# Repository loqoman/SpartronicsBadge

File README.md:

# SpartronicsBadge
The FRC Team 4915 Competition Badge

## Revision One

### Libraries
Some project specific symbols are used (Digikey slide switches). All non kicad-standard libraries used will found under `/lib/` directory, and need to be imported manually from the schematic library manager

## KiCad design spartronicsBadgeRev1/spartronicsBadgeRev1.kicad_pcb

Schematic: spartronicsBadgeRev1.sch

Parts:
BT1, BT2: Battery_Cell; BatteryHolder_Keystone_3034_1x20mm
DE1, DE2, DE3: LED; LED_0603_1608Metric_Pad1.05x0.95mm_HandSolder
DN1, DN2, DN3: LED; LED_0603_1608Metric_Pad1.05x0.95mm_HandSolder
DNE1, DNE2, DNE3: LED; LED_0603_1608Metric_Pad1.05x0.95mm_HandSolder
DNW1, DNW2, DNW3: LED; LED_0603_1608Metric_Pad1.05x0.95mm_HandSolder
DS1, DS2, DS3: LED; LED_0603_1608Metric_Pad1.05x0.95mm_HandSolder
DSE1, DSE2, DSE3: LED; LED_0603_1608Metric_Pad1.05x0.95mm_HandSolder
DSW1, DSW2, DSW3: LED; LED_0603_1608Metric_Pad1.05x0.95mm_HandSolder
DW1, DW2, DW3: LED; LED_0603_1608Metric_Pad1.05x0.95mm_HandSolder
J_Debug1: Conn_02x03; PinHeader_2x03_P2.54mm_Vertical
J_ExtPwr1: Conn_01x02; PinHeader_1x02_P2.54mm_Vertical
RE1, RE2, RE3: 220Ω; R_0603_1608Metric_Pad1.05x0.95mm_HandSolder
RN1, RN2, RN3: 220Ω; R_0603_1608Metric_Pad1.05x0.95mm_HandSolder
RNE1, RNE2, RNE3: 220Ω; R_0603_1608Metric_Pad1.05x0.95mm_HandSolder
RNW1, RNW2, RNW3: 220Ω; R_0603_1608Metric_Pad1.05x0.95mm_HandSolder
RS1, RS2, RS3: 220Ω; R_0603_1608Metric_Pad1.05x0.95mm_HandSolder
RSE1, RSE2, RSE3: 220Ω; R_0603_1608Metric_Pad1.05x0.95mm_HandSolder
RSW1, RSW2, RSW3: 220Ω; R_0603_1608Metric_Pad1.05x0.95mm_HandSolder
RW1, RW2, RW3: 220Ω; R_0603_1608Metric_Pad1.05x0.95mm_HandSolder
S1: JS202011SCQN; Switch_Slide_JS202011SCQN; MPN JS202011SCQN; Digi-Key_PN 401-2002-1-ND
U1: ATmega328PB-AU; TQFP-32_7x7mm_P0.8mm

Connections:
BAT_VCC: BT1.1 (+), J_ExtPwr1.1, S1.3, S1.6
ELED1_SIG: RE1.2, U1.10 (PD6)
ELED2_SIG: RE2.2, U1.3 (PE0)
ELED3_SIG: RE3.2, U1.2 (PD4)
GND: BT2.2 (-), DE1.1 (K), DE2.1 (K), DE3.1 (K), DN1.1 (K), DN2.1 (K), DN3.1 (K), DNE1.1 (K), DNE2.1 (K), DNE3.1 (K), DNW1.1 (K), DNW2.1 (K), DNW3.1 (K), DS1.1 (K), DS2.1 (K), DS3.1 (K), DSE1.1 (K), DSE2.1 (K), DSE3.1 (K), DSW1.1 (K), DSW2.1 (K), DSW3.1 (K), DW1.1 (K), DW2.1 (K), DW3.1 (K), J_Debug1.3, J_ExtPwr1.2, U1.5 (GND), U1.21 (GND)
MISO0: J_Debug1.6, U1.16 (PB4)
MOSI0: J_Debug1.4, U1.15 (PB3)
NC: S1.1, S1.4
NELED1_SIG: RNE1.2, U1.1 (PD3)
NELED2_SIG: RNE2.2, U1.32 (PD2)
NELED3_SIG: RNE3.2, U1.31 (PD1)
NLED1_SIG: RN3.2, U1.28 (PC5)
NLED2_SIG: RN2.2, U1.27 (PC4)
NLED3_SIG: RN1.2, U1.30 (PD0)
NWLED1_SIG: RNW1.1, U1.25 (PC2)
NWLED2_SIG: RNW2.1, U1.26 (PC3)
NWLED3_SIG: RNW3.1, U1.24 (PC1)
unnamed: BT1.2 (-), BT2.1 (+)
unnamed: DE1.2 (A), RE1.1
unnamed: DE2.2 (A), RE2.1
unnamed: DE3.2 (A), RE3.1
unnamed: DN1.2 (A), RN1.1
unnamed: DN2.2 (A), RN2.1
unnamed: DN3.2 (A), RN3.1
unnamed: DNE1.2 (A), RNE1.1
unnamed: DNE2.2 (A), RNE2.1
unnamed: DNE3.2 (A), RNE3.1
unnamed: DNW1.2 (A), RNW1.2
unnamed: DNW2.2 (A), RNW2.2
unnamed: DNW3.2 (A), RNW3.2
unnamed: DS1.2 (A), RS1.2
unnamed: DS2.2 (A), RS2.2
unnamed: DS3.2 (A), RS3.2
unnamed: DSE1.2 (A), RSE1.1
unnamed: DSE2.2 (A), RSE2.1
unnamed: DSE3.2 (A), RSE3.1
unnamed: DSW1.2 (A), RSW1.2
unnamed: DSW2.2 (A), RSW2.2
unnamed: DSW3.2 (A), RSW3.2
unnamed: DW1.2 (A), RW1.2
unnamed: DW2.2 (A), RW2.2
unnamed: DW3.2 (A), RW3.2
RESET: J_Debug1.1, U1.29 (~RESET~/PC6)
SCK0: J_Debug1.5, RSW2.1, U1.17 (PB5)
SELED1_SIG: RSE1.2, U1.14 (PB2)
SELED2_SIG: RSE2.2, U1.8 (XTAL2/PB7)
SELED3_SIG: RSE3.2, U1.6 (PE1)
SLED1_SIG: RS1.1, U1.13 (PB1)
SLED2_SIG: RS2.1, U1.11 (PD7)
SLED3_SIG: RS3.1, U1.12 (PB0)
SWLED1_SIG: RSW1.1, U1.7 (XTAL1/PB6)
SWLED3_SIG: RSW3.1, U1.9 (PD5)
VCC: J_Debug1.2, S1.2, S1.5, U1.4 (VCC)
WLED1_SIG: RW1.1, U1.22 (PE3)
WLED2_SIG: RW2.1, U1.19 (PE2)
WLED3_SIG: RW3.1, U1.23 (PC0)

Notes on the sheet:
North Tooth
North-East Tooth
East Tooth
South-East Tooth
South Tooth
West Tooth
North-West Tooth
LED Specifications:
LED Specifications
SML-LX0603SYW
20mA current
2V drop
Optional External Power
Coin cell symbols need to be assoicated with coin cell clips on netlist
Calculations for Resistors
- Resistors need to drop approx 3v
- Solve Ohms law for R when I = .02, and V = 5
- R = 5 / .02 = 250 Ω
On layout, Resistors should be renamed
Ground Plane
Label On Sickscreen
Later Revisions add reverse protection(shotkeyy) diode here?
South-West Tooth
220 ohm used due to DigiKey stock
Nb: Pin assignments look haphazard, but correspond to footprint

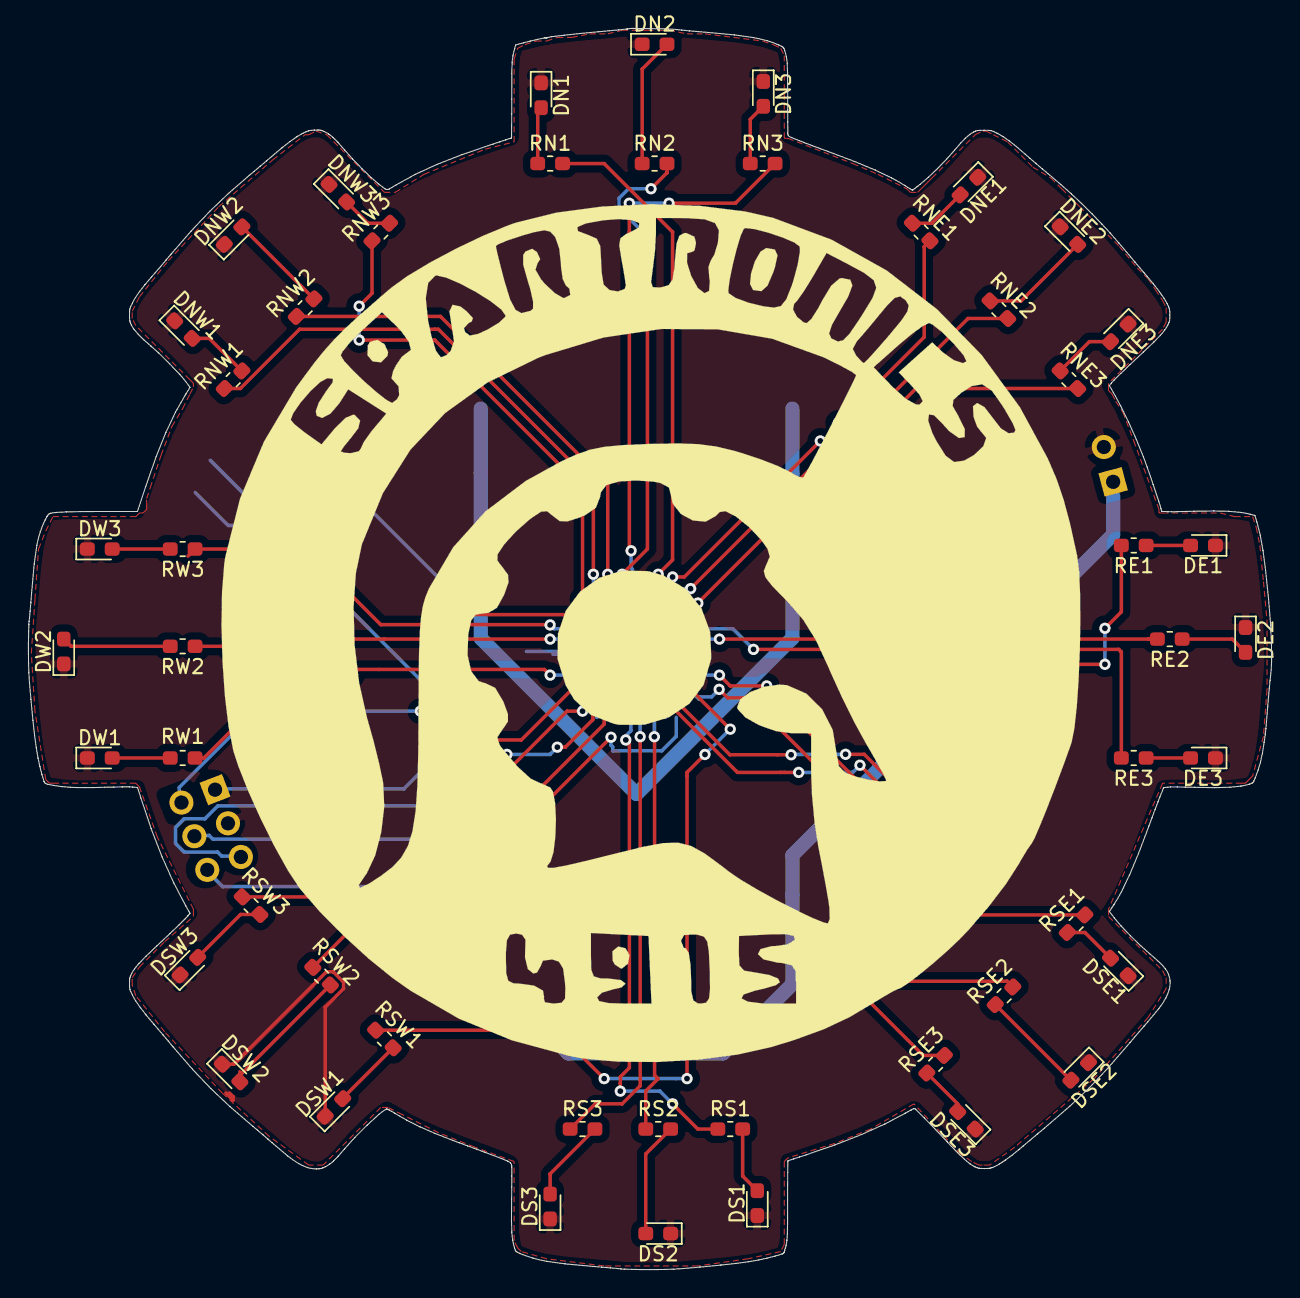
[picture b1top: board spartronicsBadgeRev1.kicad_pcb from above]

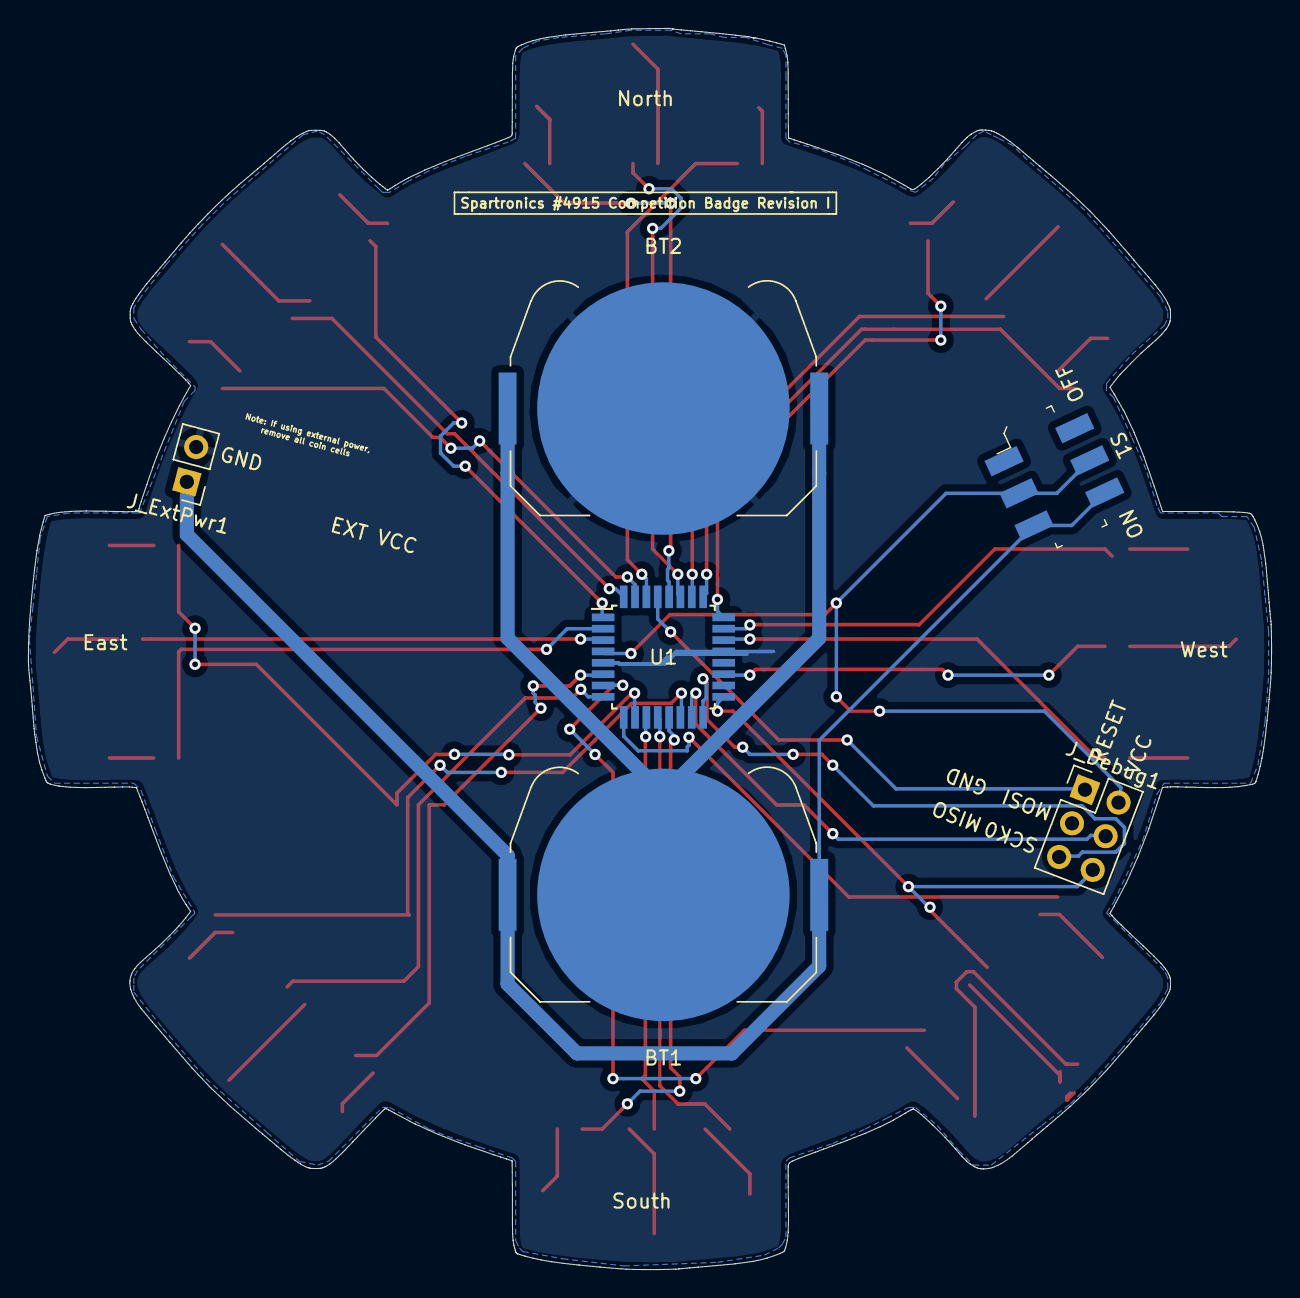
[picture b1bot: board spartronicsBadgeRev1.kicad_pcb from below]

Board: 2 copper layers, 87.6 x 87.5 mm, 54 parts (6 on the bottom side), 56 nets.

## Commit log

2019-12-27 Inital commit kicad files
2019-12-28 Some notes/changes about porting to user system
2019-12-30 Moved all the LED's to the teeth. Some silkscreen still has to be moved, need to change CON footprint + label it
2020-01-01 Checkpoint before doing routing, in case of error
2020-01-01 Finished routing, labels on back, added ground plane. Almost ready for build
2020-08-01 :package: Added a non-standard 3D model for the switch
2020-08-01 :dizzy: Re-assigning footprint to Diodes + Debug connector (Had to re-assign some pins) (Full 3D render now!)
2021-03-11 :recycle: Doing a slight formatting change in the README
